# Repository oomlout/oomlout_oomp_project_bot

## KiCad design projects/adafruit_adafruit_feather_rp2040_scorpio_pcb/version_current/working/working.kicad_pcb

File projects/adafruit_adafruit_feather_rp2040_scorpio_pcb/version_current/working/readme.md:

# OOMP Project  
## Adafruit-Feather-RP2040-SCORPIO-PCB  by adafruit  
  
oomp key: oomp_projects_flat_adafruit_adafruit_feather_rp2040_scorpio_pcb  
(snippet of original readme)  
  
-- Adafruit Feather RP2040 SCORPIO 8 Channel NeoPixel Driver PCB  
  
<a href="http://www.adafruit.com/products/5650"><br/>  
Click here to purchase one from the Adafruit shop</a>  
  
PCB files for the Adafruit Feather RP2040 SCORPIO 8 Channel NeoPixel Driver.   
  
Format is EagleCAD schematic and board layout  
* https://www.adafruit.com/product/5650  
  
--- Description  
  
If there is one thing Adafruit is known for, its mega-blinky-fun-rainbow-LEDs. We just love sticking NeoPixels anywhere and everywhere. When we saw the new 'PIO' peripheral on the RP2040 from Raspberry Pi, we just knew it would be perfect for driving large quantities of NeoPixels. So we created this board, the Adafruit Feather RP2040 SCORPIO, designed specifically for NeoPixel (WS2812) driving but also good for various other PIO-based projects that want to take advantage of the Feather pinout with 8 separate consecutive outputs (or inputs).  
  
The RP2040 PIO state machine is perfect for LED driving: it can generate perfect waveforms, with up to 8 outputs concurrently, all through DMA. That means that you don't need to use any processor time to bit-bang-out the LED data. Just set up the buffer and tell the PIO peripheral to 'make it so' and it will shove that data to the 8 outputs without delay while your code can continue to read buttons, play music, run CircuitPython - whatever you like!  
  
The SCORPIO has a clever pinout, where all the standard Feather pins are the same as the   
  full source readme at [readme_src.md](readme_src.md)  
  
source repo at: [https://github.com/adafruit/Adafruit-Feather-RP2040-SCORPIO-PCB](https://github.com/adafruit/Adafruit-Feather-RP2040-SCORPIO-PCB)  
## Board  

## Schematic  

[schematic pdf](working_schematic.pdf)  
## Images

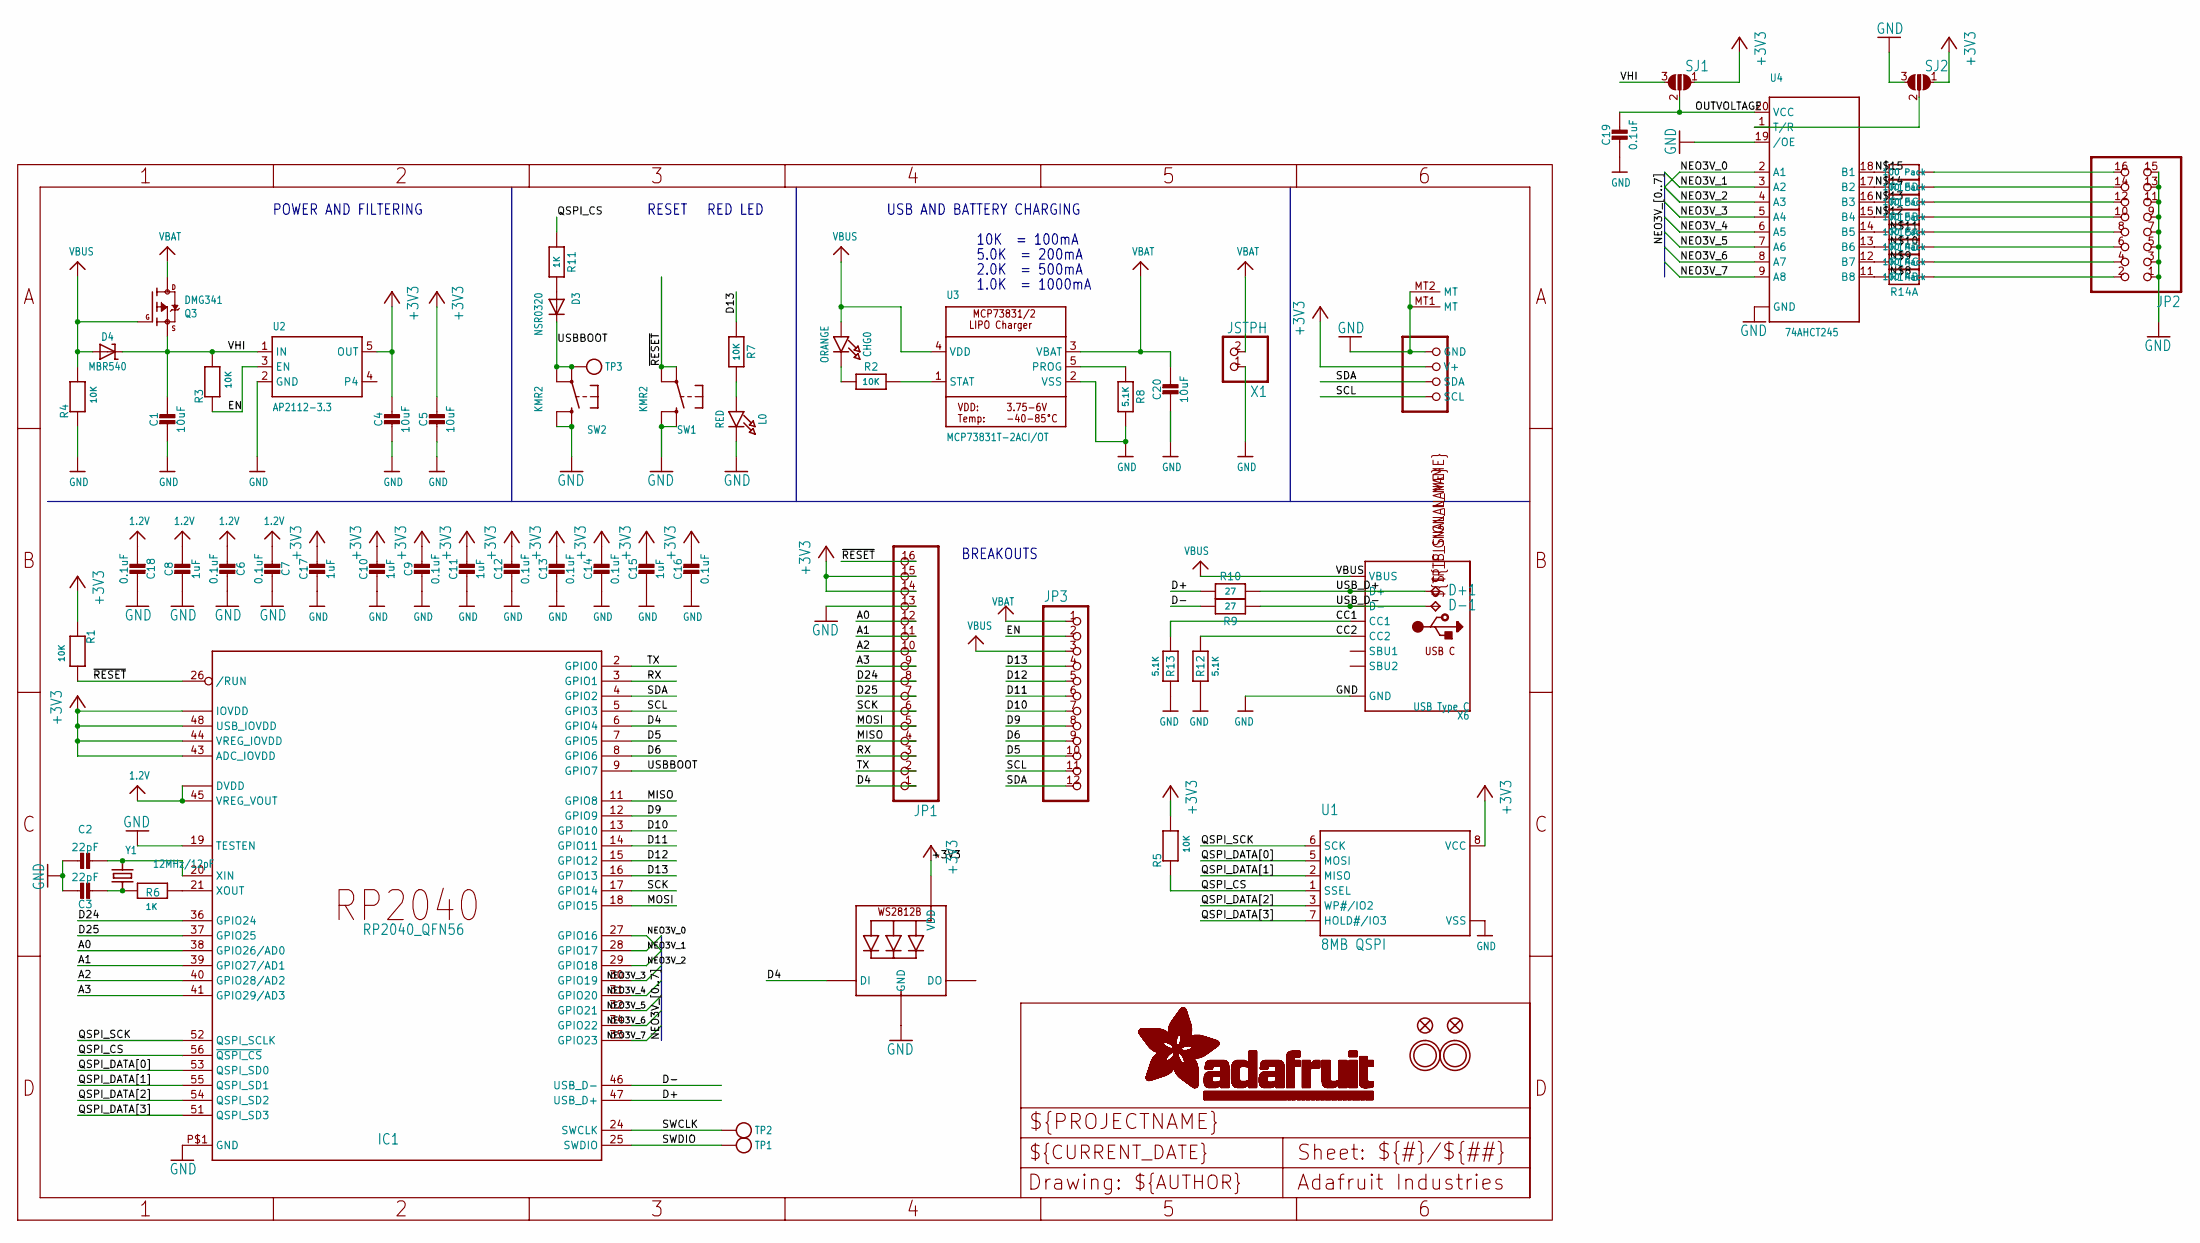
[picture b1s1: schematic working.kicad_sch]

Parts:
C1, C4, C5, C20: 10uF; 0805-NO
C2, C3: 22pF; _0402NO
C6, C7, C9, C12, C13, C14, C16, C18, C19: 0.1uF; _0402NO
C8, C10, C11, C15, C17: 1uF; 0603-NO
CHG0: ORANGE; CHIPLED_0603_NOOUTLINE
CONN1: STEMMA_I2C_QTRA; JST_SH4_RA
D3: NSR0320; SOD-323F
D4: MBR540; SOD-123
D+1: TPB1,27; B1,27
D-1: TPB1,27; B1,27
IC1: RP2040_QFN56; QFN56_7MM_REDUCEDEPAD
JP1: HEADER-1X16ROUND; 1X16_ROUND
JP2: HEADER-2X8; 2X08
JP3: HEADER-1X12; 1X12_ROUND
L0: RED; CHIPLED_0603_NOOUTLINE
LED1: WS2812B_SK6805_1515; SK6805_1515
Q3: DMG341; SOT23-R
R1, R2, R3, R4, R5, R7: 10K; 0603-NO
R6, R11: 1K; 0603-NO
R8, R12, R13: 5.1K; 0603-NO
R9, R10: 27; 0603-NO
R14, R15: 100 Pack; RESPACK_4X0402
SJ1, SJ2: SOLDERJUMPER_2WAY; SOLDERJUMPER_2WAY_OPEN_NOPASTE
SW1, SW2: KMR2; BTN_KMR2_4.6X2.8
TP1, TP2, TP3: TESTPOINTROUND1.5MMNO; TESTPOINT_ROUND_1.5MM_NO
U1: 8MB QSPI; USON8_4X4
U2: AP2112-3.3; SOT23-5; JLC_ROTATION 0
U3: MCP73831T-2ACI/OT; SOT23-5
U4: 74AHCT245; 20-DHVQFN
U$31, U$32: MOUNTINGHOLE2.5; MOUNTINGHOLE_2.5_PLATED
U$34, U$35: FIDUCIAL_1MM
X1: JSTPH; JSTPH2_BATT
X6: USB Type C; USB_C_CUSB31-CFM2AX-01-X
Y1: 12MHz/12pF; CRYSTAL_2.5X2

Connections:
1.2V: C6.2, C7.2, C8.1, C18.2, IC1.23 (DVDD), IC1.45 (VREG_VOUT), IC1.50 (DVDD)
+3V3: C4.1, C5.1, C9.1, C10.1, C11.1, C12.1, C13.1, C14.1, C15.1, C16.1, C17.1, CONN1.2 (V+), IC1.1 (IOVDD), IC1.10 (IOVDD), IC1.22 (IOVDD), IC1.33 (IOVDD), IC1.42 (IOVDD), IC1.43 (ADC_IOVDD), IC1.44 (VREG_IOVDD), IC1.48 (USB_IOVDD), IC1.49 (IOVDD), JP1.14, JP1.15, LED1.2 (VDD), R1.1, R5.2, SJ1.1, SJ2.1, U1.8 (VCC), U2.5 (OUT)
A0: IC1.38 (GPIO26/AD0), JP1.12
A1: IC1.39 (GPIO27/AD1), JP1.11
A2: IC1.40 (GPIO28/AD2), JP1.10
A3: IC1.41 (GPIO29/AD3), JP1.9
CC1: R13.2, X6.A5 (CC1)
CC2: R12.2, X6.B5 (CC2)
D4: IC1.6 (GPIO4), JP1.1, LED1.1 (DI)
D5: IC1.7 (GPIO5), JP3.10
D6: IC1.8 (GPIO6), JP3.9
D9: IC1.12 (GPIO9), JP3.8
D10: IC1.13 (GPIO10), JP3.7
D11: IC1.14 (GPIO11), JP3.6
D12: IC1.15 (GPIO12), JP3.5
D13: IC1.16 (GPIO13), JP3.4, R7.1
D24: IC1.36 (GPIO24), JP1.8
D25: IC1.37 (GPIO25), JP1.7
D+: IC1.47 (USB_D+), R10.2
D-: IC1.46 (USB_D-), R9.2
EN: JP3.2, R3.1, U2.3 (EN)
GND: C1.2, C2.1, C3.1, C4.2, C5.2, C6.1, C7.1, C8.2, C9.2, C10.2, C11.2, C12.2, C13.2, C14.2, C15.2, C16.2, C17.2, C18.1, C19.2, C20.2, CONN1.1 (GND), CONN1.MT1 (MT), CONN1.MT2 (MT), IC1.19 (TESTEN), IC1.P$1 (GND), JP1.13, JP2.1, JP2.3, JP2.5, JP2.7, JP2.9, JP2.11, JP2.13, JP2.15, L0.C, LED1.4 (GND), R4.1, R8.2, R12.1, R13.1, SJ2.3, SW1.B (S), SW1.B' (S1), SW2.B (S), SW2.B' (S1), U1.4 (VSS), U1.PAD (VSS), U2.2 (GND), U3.2 (VSS), U4.10 (GND), U4.19 (/OE), U4.21 (GND), X1.1, X6.A1B12 (GND), X6.B1A12 (GND)
MISO: IC1.11 (GPIO8), JP1.4
MOSI: IC1.18 (GPIO15), JP1.5
unnamed: CHG0.C, R2.1
unnamed: L0.A, R7.2
unnamed: R2.2, U3.1 (STAT)
unnamed: R8.1, U3.5 (PROG)
unnamed: C2.2, IC1.20 (XIN), Y1.3 (2)
unnamed: C3.2, R6.1, Y1.1
unnamed: IC1.21 (XOUT), R6.2
unnamed: R14.8 (2), U4.11 (B8)
unnamed: R14.7 (2), U4.12 (B7)
unnamed: R14.6 (2), U4.13 (B6)
unnamed: R14.5 (2), U4.14 (B5)
unnamed: R15.8 (2), U4.15 (B4)
unnamed: R15.7 (2), U4.16 (B3)
unnamed: R15.6 (2), U4.17 (B2)
unnamed: R15.5 (2), U4.18 (B1)
unnamed: D3.A, R11.2
unnamed: SJ2.2, U4.1 (T/R)
NEO0: JP2.16, R15.4 (1)
NEO1: JP2.14, R15.3 (1)
NEO2: JP2.12, R15.2 (1)
NEO3: JP2.10, R15.1
NEO3V_0: IC1.27 (GPIO16), U4.2 (A1)
NEO3V_1: IC1.28 (GPIO17), U4.3 (A2)
NEO3V_2: IC1.29 (GPIO18), U4.4 (A3)
NEO3V_3: IC1.30 (GPIO19), U4.5 (A4)
NEO3V_4: IC1.31 (GPIO20), U4.6 (A5)
NEO3V_5: IC1.32 (GPIO21), U4.7 (A6)
NEO3V_6: IC1.34 (GPIO22), U4.8 (A7)
NEO3V_7: IC1.35 (GPIO23), U4.9 (A8)
NEO4: JP2.8, R14.4 (1)
NEO5: JP2.6, R14.3 (1)
NEO6: JP2.4, R14.2 (1)
NEO7: JP2.2, R14.1
OUTVOLTAGE: C19.1, SJ1.2, U4.20 (VCC)
QSPI_CS: IC1.56 (~QSPI_CS), R5.1, R11.1, U1.1 (SSEL)
QSPI_DATA[0]: IC1.53 (QSPI_SD0), U1.5 (MOSI)
QSPI_DATA[1]: IC1.55 (QSPI_SD1), U1.2 (MISO)
QSPI_DATA[2]: IC1.54 (QSPI_SD2), U1.3 (WP#/IO2)
QSPI_DATA[3]: IC1.51 (QSPI_SD3), U1.7 (HOLD#/IO3)
QSPI_SCK: IC1.52 (QSPI_SCLK), U1.6 (SCK)
RX: IC1.3 (GPIO1), JP1.3
SCK: IC1.17 (GPIO14), JP1.6
SCL: CONN1.4 (SCL), IC1.5 (GPIO3), JP3.11
SDA: CONN1.3 (SDA), IC1.4 (GPIO2), JP3.12
SWCLK: IC1.24 (SWCLK), TP2.P$1
SWDIO: IC1.25 (SWDIO), TP1.P$1
TX: IC1.2 (GPIO0), JP1.2
USBBOOT: D3.C, IC1.9 (GPIO7), SW2.A, SW2.A' (P1), TP3.P$1
USB_D+: D+1.TP, R10.1, X6.A6 (D+), X6.B6 (D+)
USB_D-: D-1.TP, R9.1, X6.A7 (D-), X6.B7 (D-)
VBAT: C20.1, JP3.1, Q3.3 (D), U3.3 (VBAT), X1.2
VBUS: CHG0.A, D4.A, JP3.3, Q3.1 (G), R4.2, U3.4 (VDD), X6.A4B9 (VBUS), X6.B4A9 (VBUS)
VHI: C1.1, D4.C, Q3.2 (S), R3.2, SJ1.3, U2.1 (IN)
~RESET: IC1.26 (/RUN), JP1.16, R1.2, SW1.A, SW1.A' (P1)

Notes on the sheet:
5.0K = 200mA
POWER AND FILTERING
10K = 100mA
BREAKOUTS
1.0K = 1000mA
USB AND BATTERY CHARGING
RESET
RED LED
2.0K = 500mA

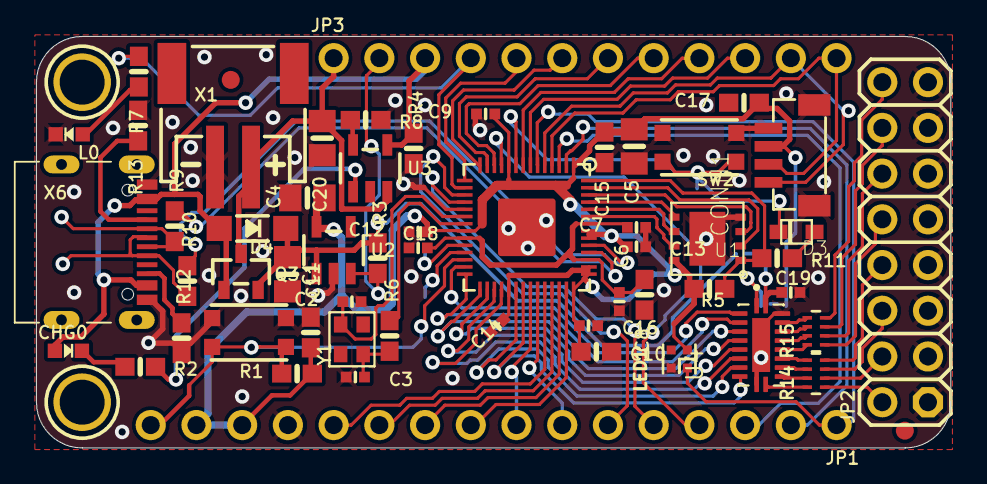
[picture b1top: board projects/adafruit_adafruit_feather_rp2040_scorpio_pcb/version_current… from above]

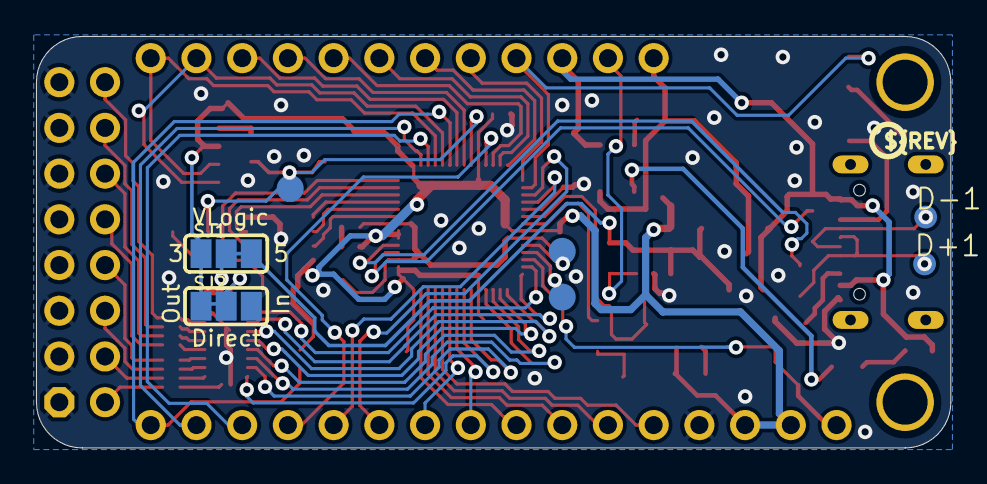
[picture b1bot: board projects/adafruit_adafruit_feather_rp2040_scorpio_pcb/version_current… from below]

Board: 2 copper layers, 50.8 x 22.9 mm, 69 parts (9 on the bottom side), 78 nets.

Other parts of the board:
U$12: SCORPIO_TOP
U$13: PCBFEAT-REV-040
U$28: SCORPIO_BOT

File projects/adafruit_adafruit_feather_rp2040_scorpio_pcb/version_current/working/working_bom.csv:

Row,Description,Part,References,Value,Footprint,Quantity Per PCB,Status,Datasheet,JLC_ROTATION,REV
1,,CAP_CERAMIC_0402NO,C2 C3,22pF,_0402NO,2, ,,,
2,,CAP_CERAMIC_0402NO,C6 C7 C9 C12 C13 C14 C16 C18 C19,0.1uF,_0402NO,9, ,,,
3,,CAP_CERAMIC0603_NO,C8 C10 C11 C15 C17,1uF,0603-NO,5, ,,,
4,,CAP_CERAMIC0805-NOOUTLINE,C1 C4 C5 C20,10uF,0805-NO,4, ,,,A
5,,LED0603_NOOUTLINE,CHG0,ORANGE,CHIPLED_0603_NOOUTLINE,1, ,,,
6,,STEMMA_I2C_QTRA,CONN1,STEMMA_I2C_QTRA,JST_SH4_RA,1, ,,,
7,,DIODE-SCHOTTKYSOD-123,D4,MBR540,SOD-123,1, ,,,
8,,DIODESOD-323F,D3,NSR0320,SOD-323F,1, ,,,
9,,"TPB1,27",D+1 D-1,"TPB1,27","B1,27",2, ,,,
10,,RP2040_QFN56,IC1,RP2040_QFN56,QFN56_7MM_REDUCEDEPAD,1, ,,,
11,,HEADER-1X12,JP3,HEADER-1X12,1X12_ROUND,1, ,,,
12,,HEADER-1X16ROUND,JP1,HEADER-1X16ROUND,1X16_ROUND,1, ,,,
13,,HEADER-2X8,JP2,HEADER-2X8,2X08,1, ,,,
14,,LED0603_NOOUTLINE,L0,RED,CHIPLED_0603_NOOUTLINE,1, ,,,
15,,WS2812B_SK6805_1515,LED1,WS2812B_SK6805_1515,SK6805_1515,1, ,,,
16,,MOSFET-P,Q3,DMG341,SOT23-R,1, ,,,
17,,RESISTOR_0603_NOOUT,R9 R10,27,0603-NO,2, ,,,
18,,RESISTOR_4PACK_0804,R14 R15,100 Pack,RESPACK_4X0402,2, ,,,
19,,RESISTOR_0603_NOOUT,R6 R11,1K,0603-NO,2, ,,,
20,,RESISTOR_0603_NOOUT,R8 R12 R13,5.1K,0603-NO,3, ,,,
21,,RESISTOR_0603_NOOUT,R1 R2 R3 R4 R5 R7,10K,0603-NO,6, ,,,
22,,SWITCH_TACT_SMT4.6X2.8,SW1 SW2,KMR2,BTN_KMR2_4.6X2.8,2, ,,,
23,,74LCX245_QFN20,U4,74AHCT245,20-DHVQFN,1, ,,,
24,,SPIFLASH_8PIN_4X4,U1,8MB QSPI,USON8_4X4,1, ,,,
25,,VREG_SOT23-5,U2,AP2112-3.3,SOT23-5,1, ,,0,
26,,MCP73831/2,U3,MCP73831T-2ACI/OT,SOT23-5,1, ,,,
27,,CON_JST_PH_2PIN_BATT,X1,JSTPH,JSTPH2_BATT,1, ,,,
28,,USB_C,X6,USB Type C,USB_C_CUSB31-CFM2AX-01-X,1, ,,,
29,,CRYSTAL2.5X2.0,Y1,12MHz/12pF,CRYSTAL_2.5X2,1, ,,,





Project info:
Schematic:,working
Variant:,default
Revision:,
Date:,2023-08-02_17-08-33
KiCad Version:,7.0.6-7.0.6~ubuntu22.04.1
Statistics:
Component Groups:,29
Component Count:,57 (0 SMD/ 0 THT)
Fitted Components:,57 (0 SMD/ 0 THT)
Number of PCBs:,1
Total Components:,57

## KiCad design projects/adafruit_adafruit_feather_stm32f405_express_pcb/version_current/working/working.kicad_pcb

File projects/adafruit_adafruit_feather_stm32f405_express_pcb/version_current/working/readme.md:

# OOMP Project  
## Adafruit-Feather-STM32F405-Express-PCB  by adafruit  
  
oomp key: oomp_projects_flat_adafruit_adafruit_feather_stm32f405_express_pcb  
(snippet of original readme)  
  
-- Adafruit Adafruit Feather STM32F405 Express PCB  
  
<a href="http://www.adafruit.com/products/4382"><br/>  
Click here to purchase one from the Adafruit shop</a>  
  
PCB files for the Adafruit Adafruit Feather STM32F405 Express.   
  
Format is EagleCAD schematic and board layout  
* https://www.adafruit.com/product/4382  
  
--- Description  
  
ST takes flight in this upcoming Feather board. The new STM32F405 Feather (video) that we designed runs CircuitPython at a blistering 168MHz – our fastest CircuitPython board ever! We put a STEMMA QT / Qwiic port on the end, so you can really easily plug and play I2C sensors.  
  
This Feather has lots of goodies:  
  
* STM32F405 Cortex M4 with FPU and 1MB Flash, 168MHz speed  
* 192KB RAM total - 128 KB RAM for general usage + 64 KB program-only/cache RAM  
* 3.3V logic, but almost all pins are 5V compliant!  
* USB C power and data - our first USB C Feather!  
* LiPo connector and charger  
* SD socket on the bottom, connected to SDIO port  
* 2 MB SPI Flash chip  
* Built in NeoPixel indicator  
* I2C, UART, GPIO, ADCs, DACs  
* Qwiic/STEMMA-QT connector for fast I2C connectivity  
* We use the built-in USB DFU bootloader to load firmware. It does not come with a UF2 bootloader.  
  
With CircuitPython basics running on this board, it's fast to get all our drivers working, then use the built in plotter in Mu to instantly get sensor data displaying within 3 minutes of unboxing.  
  
You can use MicroPython, CircuitPython or Arduino IDE  
  full source readme at [readme_src.md](readme_src.md)  
  
source repo at: [https://github.com/adafruit/Adafruit-Feather-STM32F405-Express-PCB](https://github.com/adafruit/Adafruit-Feather-STM32F405-Express-PCB)  
## Board  

## Schematic  

[schematic pdf](working_schematic.pdf)  
## Images

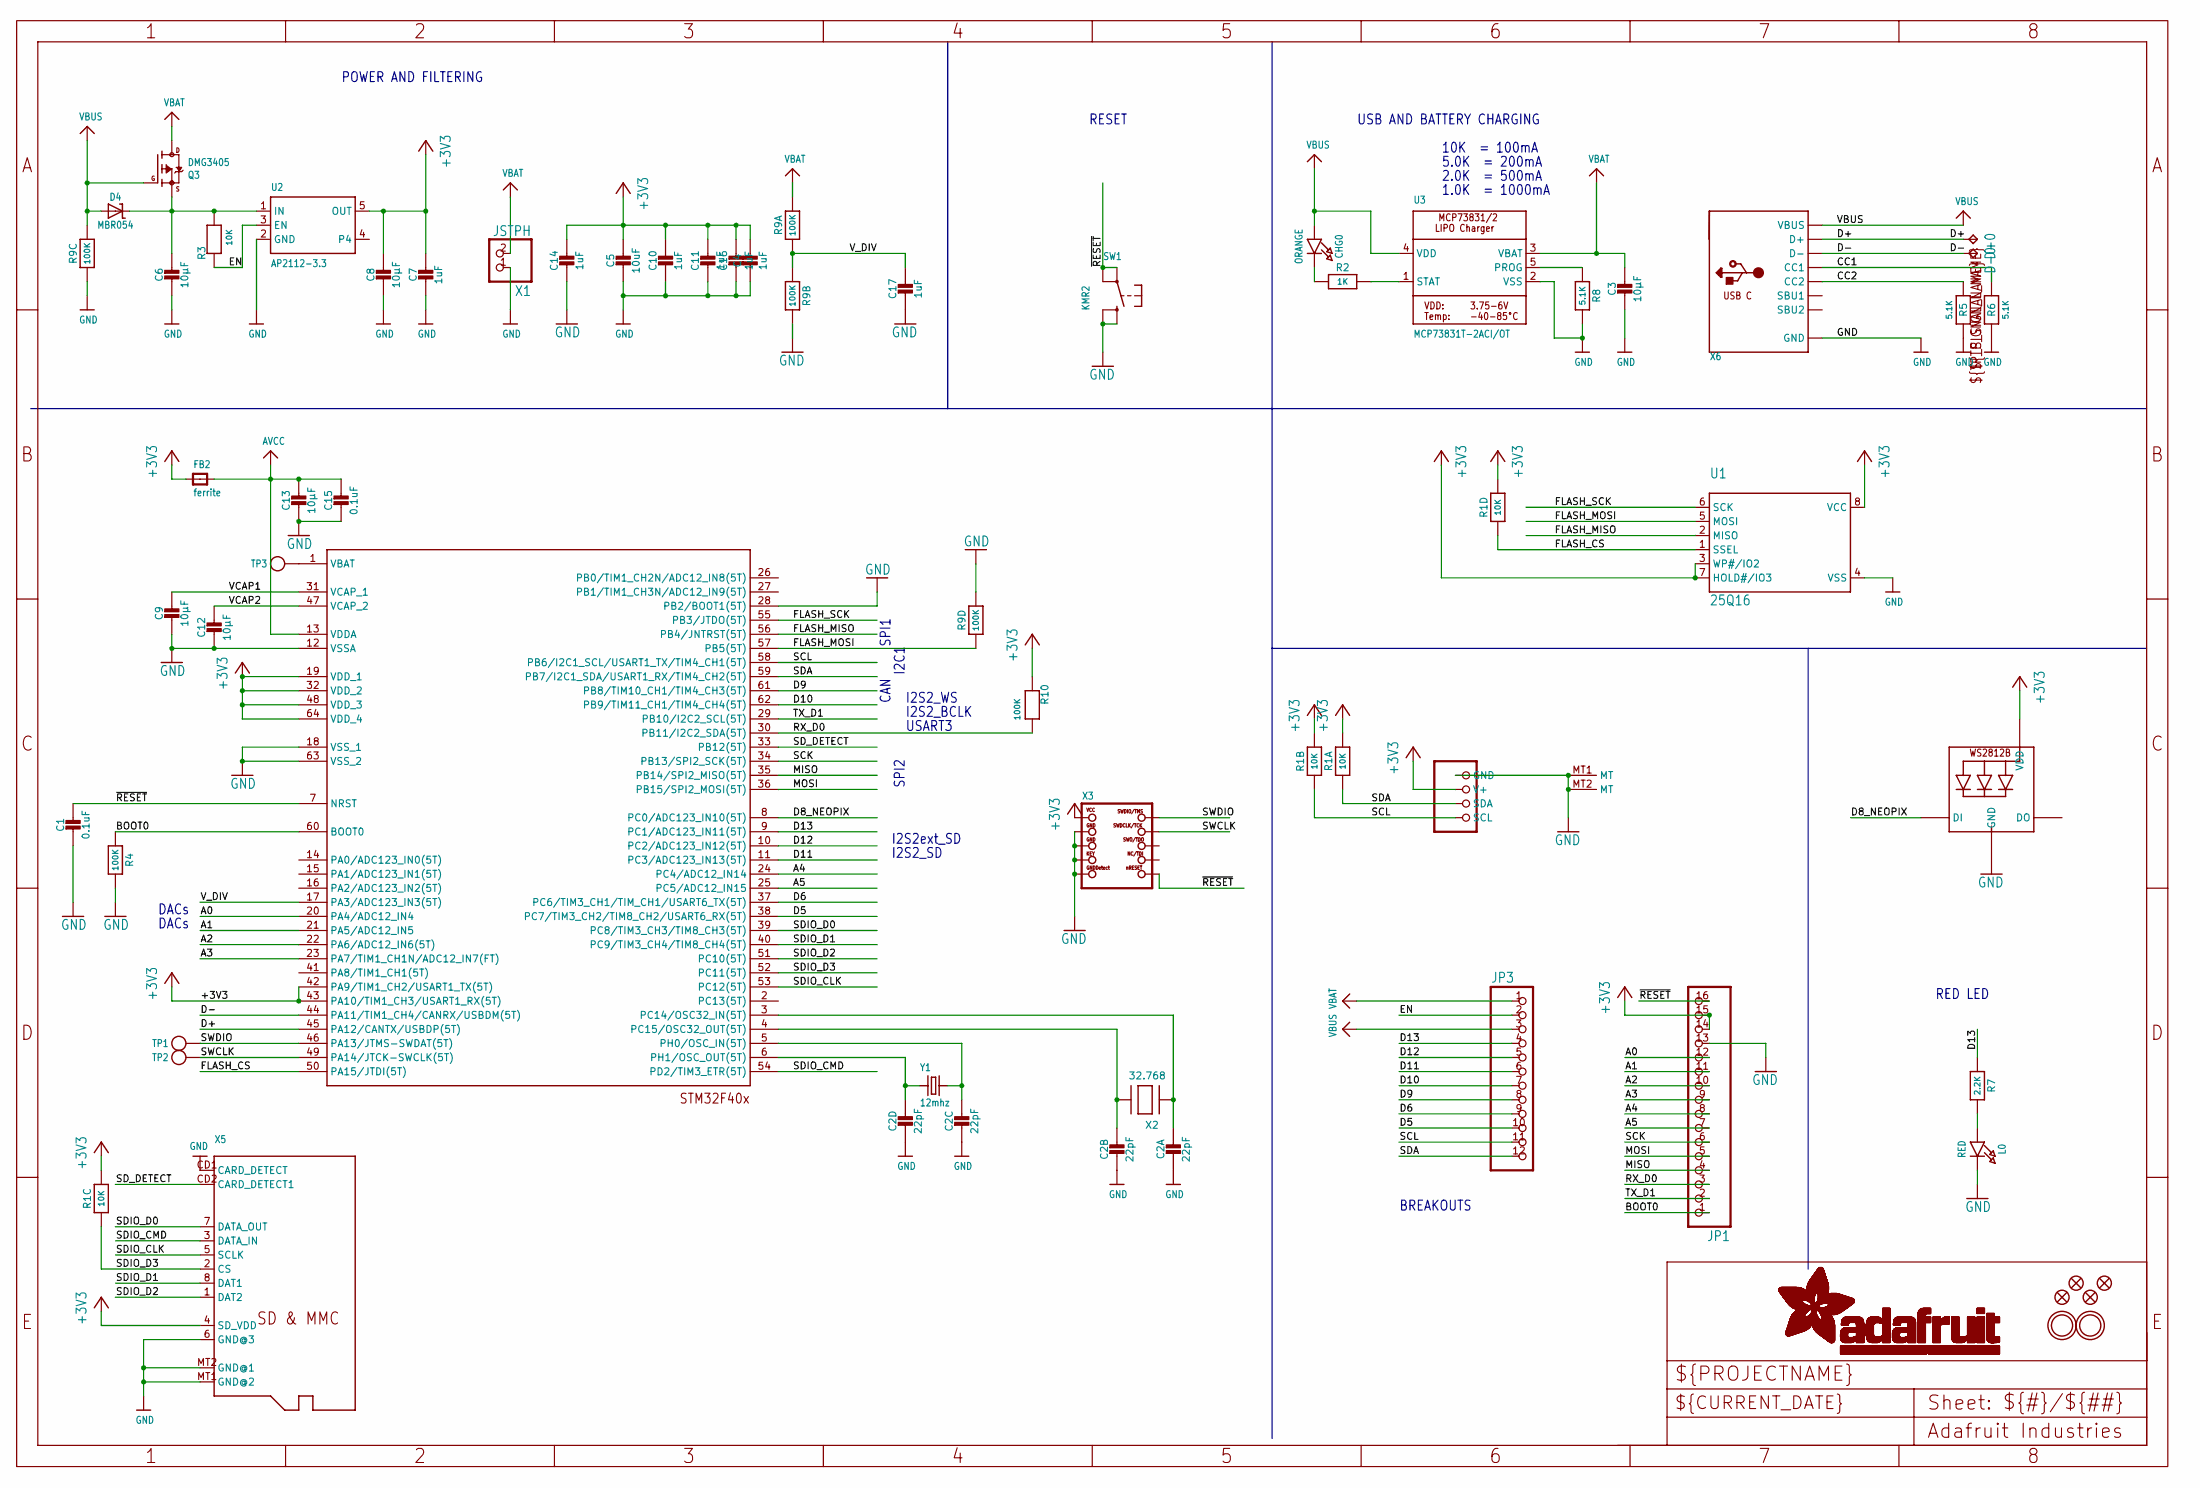
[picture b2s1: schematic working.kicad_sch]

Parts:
C1, C15: 0.1uF; 0603-NO
C2: 22pF; RESPACK_4X0603
C3, C6, C8, C9, C12, C13: 10µF; 0805-NO
C4, C7, C10, C11, C14, C16, C17: 1uF; 0603-NO
C5: 10uF; 0805-NO
CHG0: ORANGE; CHIPLED_0805_NOOUTLINE
CONN1: STEMMA_I2C_QT; JST_SH4
D4: MBR054; SOD-123
D+0: TPB1,27; B1,27
D-0: TPB1,27; B1,27
FB2: ferrite; 0805-NO
JP1: HEADER-1X16ROUND; 1X16_ROUND
JP3: HEADER-1X12; 1X12_ROUND
L0: RED; CHIPLED_0805_NOOUTLINE
LED1: WS2812B3535; LED3535
Q3: DMG3405; SOT23-R
R1: 10K; RESPACK_4X0603_NO
R2: 1K; 0603-NO
R3: 10K; 0603-NO
R4, R10: 100K; 0603-NO
R5, R6, R8: 5.1K; 0603-NO
R7: 2.2K; 0603-NO
R9: 100K; RESPACK_4X0603_NO
SW1: KMR2; BTN_KMR2_4.6X2.8
TP1, TP2, TP3: TESTPOINTROUND1.5MM; TESTPOINT_ROUND_1.5MM
U1: 25Q16; SOIC8_150MIL
U2: AP2112-3.3; SOT23-5
U3: MCP73831T-2ACI/OT; SOT23-5
U$3: STM32F405R; TQFP64
U$5, U$34, U$35, U$37: FIDUCIAL_1MM
U$31, U$32: MOUNTINGHOLE2.5; MOUNTINGHOLE_2.5_PLATED
X1: JSTPH; JSTPH2
X2: 32.768; XTAL3215
X3: JTAG-CORTEX; 2X05_1.27MM_SMT
X5: MICROSD
X6: USB_C; USB_C_CUSB31-CFM2AX-01-X
Y1: 12mhz; CRYSTAL_2.5X2

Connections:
+3V3: C4.1, C5.1, C7.1, C8.1, C10.1, C11.1, C14.1, C16.1, CONN1.2 (V+), FB2.1, JP1.14, JP1.15, LED1.2 (VDD), R1.5 (2), R1.6 (2), R1.7 (2), R1.8 (2), R10.1, U1.3 (WP#/IO2), U1.7 (HOLD#/IO3), U1.8 (VCC), U2.5 (OUT), U$3.19 (VDD_1), U$3.32 (VDD_2), U$3.42 (PA9/TIM1_CH2/USART1_TX(5T)), U$3.43 (PA10/TIM1_CH3/USART1_RX(5T)), U$3.48 (VDD_3), U$3.64 (VDD_4), X3.1 (VCC), X5.4 (SD_VDD)
A0: JP1.12, U$3.20 (PA4/ADC12_IN4)
A1: JP1.11, U$3.21 (PA5/ADC12_IN5)
A2: JP1.10, U$3.22 (PA6/ADC12_IN6(5T))
A3: JP1.9, U$3.23 (PA7/TIM1_CH1N/ADC12_IN7(FT))
A4: JP1.8, U$3.24 (PC4/ADC12_IN14)
A5: JP1.7, U$3.25 (PC5/ADC12_IN15)
AVCC: C13.1, C15.1, FB2.2, U$3.13 (VDDA)
BATTERY: TP3.P$1, U$3.1 (VBAT)
BOOT0: JP1.1, R4.1, U$3.60 (BOOT0)
CC1: R6.2, X6.A5 (CC1)
CC2: R5.2, X6.B5 (CC2)
D5: JP3.10, U$3.38 (PC7/TIM3_CH2/TIM8_CH2/USART6_RX(5T))
D6: JP3.9, U$3.37 (PC6/TIM3_CH1/TIM_CH1/USART6_TX(5T))
D8_NEOPIX: LED1.1 (DI), U$3.8 (PC0/ADC123_IN10(5T))
D9: JP3.8, U$3.61 (PB8/TIM10_CH1/TIM4_CH3(5T))
D10: JP3.7, U$3.62 (PB9/TIM11_CH1/TIM4_CH4(5T))
D11: JP3.6, U$3.11 (PC3/ADC123_IN13(5T))
D12: JP3.5, U$3.10 (PC2/ADC123_IN12(5T))
D13: JP3.4, R7.1, U$3.9 (PC1/ADC123_IN11(5T))
D+: D+0.TP, U$3.45 (PA12/CANTX/USBDP(5T)), X6.A6 (D+), X6.B6 (D+)
D-: D-0.TP, U$3.44 (PA11/TIM1_CH4/CANRX/USBDM(5T)), X6.A7 (D-), X6.B7 (D-)
EN: JP3.2, R3.1, U2.3 (EN)
FLASH_CS: R1.4 (1), U1.1 (SSEL), U$3.50 (PA15/JTDI(5T))
FLASH_MISO: U1.2 (MISO), U$3.56 (PB4/JNTRST(5T))
FLASH_MOSI: R9.4 (1), U1.5 (MOSI), U$3.57 (PB5(5T))
FLASH_SCK: U1.6 (SCK), U$3.55 (PB3/JTDO(5T))
GND: C1.2, C2.5 (2), C2.6 (2), C2.7 (2), C2.8 (2), C3.2, C4.2, C5.2, C6.2, C7.2, C8.2, C9.2, C10.2, C11.2, C12.2, C13.2, C14.2, C15.2, C16.2, C17.2, CONN1.1 (GND), CONN1.MT1 (MT), CONN1.MT2 (MT), JP1.13, L0.C, LED1.4 (GND), R4.2, R5.1, R6.1, R8.2, R9.3 (1), R9.5 (2), R9.7 (2), SW1.B (S), SW1.B' (S1), U1.4 (VSS), U2.2 (GND), U3.2 (VSS), U$3.12 (VSSA), U$3.18 (VSS_1), U$3.28 (PB2/BOOT1(5T)), U$3.63 (VSS_2), X1.1, X3.3 (GND@1), X3.5 (GND@2), X3.7 (KEY), X3.9 (GNDDETECT), X5.6 (GND@3), X5.CD1 (CARD_DETECT), X5.MT1 (GND@2), X5.MT2 (GND@1), X6.A1B12 (GND), X6.B1A12 (GND)
MISO: JP1.4, U$3.35 (PB14/SPI2_MISO(5T))
MOSI: JP1.5, U$3.36 (PB15/SPI2_MOSI(5T))
unnamed: CHG0.C, R2.1
unnamed: L0.A, R7.2
unnamed: R2.2, U3.1 (STAT)
unnamed: R8.1, U3.5 (PROG)
unnamed: C2.4 (1), U$3.3 (PC14/OSC32_IN(5T)), X2.P$1
unnamed: C2.2 (1), U$3.5 (PH0/OSC_IN(5T)), Y1.3 (2)
unnamed: C2.3 (1), U$3.4 (PC15/OSC32_OUT(5T)), X2.P$2
unnamed: C2.1, U$3.6 (PH1/OSC_OUT(5T)), Y1.1
RX_D0: JP1.3, R10.2, U$3.30 (PB11/I2C2_SDA(5T))
SCK: JP1.6, U$3.34 (PB13/SPI2_SCK(5T))
SCL: CONN1.4 (SCL), JP3.11, R1.2 (1), U$3.58 (PB6/I2C1_SCL/USART1_TX/TIM4_CH1(5T))
SDA: CONN1.3 (SDA), JP3.12, R1.1, U$3.59 (PB7/I2C1_SDA/USART1_RX/TIM4_CH2(5T))
SDIO_CLK: U$3.53 (PC12(5T)), X5.5 (SCLK)
SDIO_CMD: U$3.54 (PD2/TIM3_ETR(5T)), X5.3 (DATA_IN)
SDIO_D0: U$3.39 (PC8/TIM3_CH3/TIM8_CH3(5T)), X5.7 (DATA_OUT)
SDIO_D1: U$3.40 (PC9/TIM3_CH4/TIM8_CH4(5T)), X5.8 (DAT1)
SDIO_D2: U$3.51 (PC10(5T)), X5.1 (DAT2)
SDIO_D3: R1.3 (1), U$3.52 (PC11(5T)), X5.2 (CS)
SD_DETECT: U$3.33 (PB12(5T)), X5.CD2 (CARD_DETECT1)
SWCLK: TP2.P$1, U$3.49 (PA14/JTCK-SWCLK(5T)), X3.4 (SWDCLK)
SWDIO: TP1.P$1, U$3.46 (PA13/JTMS-SWDAT(5T)), X3.2 (SWDIO)
TX_D1: JP1.2, U$3.29 (PB10/I2C2_SCL(5T))
VBAT: C3.1, JP3.1, Q3.3 (D), R9.8 (2), U3.3 (VBAT), X1.2
VBUS: CHG0.A, D4.A, JP3.3, Q3.1 (G), R9.6 (2), U3.4 (VDD), X6.A4B9 (VBUS), X6.B4A9 (VBUS)
VCAP1: C9.1, U$3.31 (VCAP_1)
VCAP2: C12.1, U$3.47 (VCAP_2)
VHI: C6.1, D4.C, Q3.2 (S), R3.2, U2.1 (IN)
V_DIV: C17.1, R9.1, R9.2 (1), U$3.17 (PA3/ADC123_IN3(5T))
~RESET: C1.1, JP1.16, SW1.A, SW1.A' (P1), U$3.7 (NRST), X3.10 (NRESET)

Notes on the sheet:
BREAKOUTS
POWER AND FILTERING
DACs
USART3
1.0K = 1000mA
I2S2_BCLK
CAN
RESET
10K = 100mA
I2C1
SPI2
USB AND BATTERY CHARGING
I2S2ext_SD
I2S2_SD
RED LED
SPI1
2.0K = 500mA
5.0K = 200mA
I2S2_WS

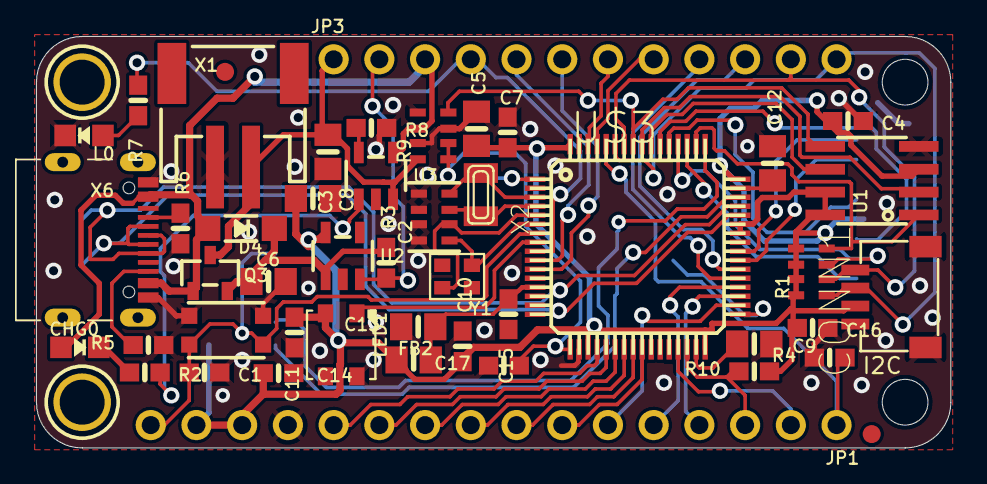
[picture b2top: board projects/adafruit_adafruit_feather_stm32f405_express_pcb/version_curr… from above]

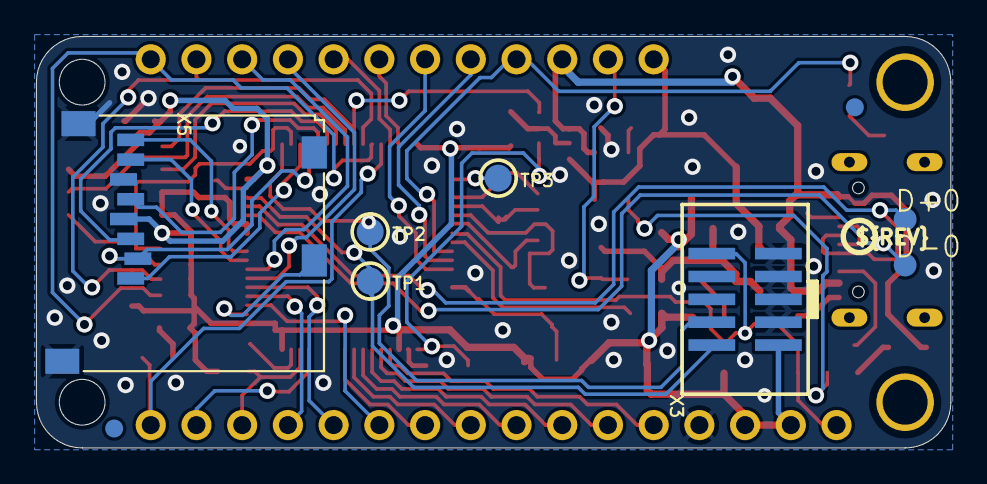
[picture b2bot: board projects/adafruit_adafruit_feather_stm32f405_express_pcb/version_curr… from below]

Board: 2 copper layers, 50.8 x 22.9 mm, 63 parts (11 on the bottom side), 59 nets.

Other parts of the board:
@HOLE0, @HOLE1: (no value)
U$13: PCBFEAT-REV-040
U$24: FEATHER_STM32F405_TOP
U$40: FEATHER_STM32F405_BOT

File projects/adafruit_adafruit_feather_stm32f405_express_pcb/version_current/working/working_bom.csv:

Row,Description,Part,References,Value,Footprint,Quantity Per PCB,Status,Datasheet,REV
1,,CAP_4PACK1206,C2,22pF,RESPACK_4X0603,1, ,,
2,,CAP_CERAMIC0603_NO,C1 C15,0.1uF,0603-NO,2, ,,
3,,CAP_CERAMIC0603_NO,C4 C7 C10 C11 C14 C16 C17,1uF,0603-NO,7, ,,
4,,CAP_CERAMIC0805-NOOUTLINE,C3 C5 C6 C8 C9 C12 C13,10µF,0805-NO,7, ,,B
5,,LED0805_NOOUTLINE,CHG0,ORANGE,CHIPLED_0805_NOOUTLINE,1, ,,
6,,STEMMA_I2C_QT,CONN1,STEMMA_I2C_QT,JST_SH4,1, ,,
7,,DIODE-SCHOTTKYSOD-123,D4,MBR054,SOD-123,1, ,,
8,,"TPB1,27",D+0 D-0,"TPB1,27","B1,27",2, ,,
9,,FERRITE-0805NO,FB2,ferrite,0805-NO,1, ,,
10,,HEADER-1X12,JP3,HEADER-1X12,1X12_ROUND,1, ,,
11,,HEADER-1X16ROUND,JP1,HEADER-1X16ROUND,1X16_ROUND,1, ,,
12,,LED0805_NOOUTLINE,L0,RED,CHIPLED_0805_NOOUTLINE,1, ,,
13,,WS2812B3535,LED1,WS2812B3535,LED3535,1, ,,
14,,MOSFET-P,Q3,DMG3405,SOT23-R,1, ,,
15,,RESISTOR_0603_NOOUT,R2,1K,0603-NO,1, ,,
16,,RESISTOR_0603_NOOUT,R7,2.2K,0603-NO,1, ,,
17,,RESISTOR_0603_NOOUT,R5 R6 R8,5.1K,0603-NO,3, ,,
18,,RESISTOR_4PACK_NO,R1,10K,RESPACK_4X0603_NO,1, ,,
19,,RESISTOR_0603_NOOUT,R3,10K,0603-NO,1, ,,
20,,RESISTOR_0603_NOOUT,R4 R10,100K,0603-NO,2, ,,
21,,RESISTOR_4PACK_NO,R9,100K,RESPACK_4X0603_NO,1, ,,
22,,SWITCH_TACT_SMT4.6X2.8,SW1,KMR2,BTN_KMR2_4.6X2.8,1, ,,
23,,SPIFLASH_8PIN,U1,25Q16,SOIC8_150MIL,1, ,,
24,,VREG_SOT23-5,U2,AP2112-3.3,SOT23-5,1, ,,
25,,MCP73831/2,U3,MCP73831T-2ACI/OT,SOT23-5,1, ,,
26,,STM32F405R,U$3,STM32F405R,TQFP64,1, ,,
27,,XTAL-3.2X1.5,X2,32.768,XTAL3215,1, ,,
28,,CON_JST_PH_2PIN,X1,JSTPH,JSTPH2,1, ,,
29,,JTAG-CORTEX,X3,JTAG-CORTEX,2X05_1.27MM_SMT,1, ,,
30,,MICROSD,X5,MICROSD,MICROSD,1, ,,
31,,USB_C,X6,USB_C,USB_C_CUSB31-CFM2AX-01-X,1, ,,
32,,CRYSTAL2.5X2.0,Y1,12mhz,CRYSTAL_2.5X2,1, ,,





Project info:
Schematic:,working
Variant:,default
Revision:,
Date:,2023-08-02_17-08-33
KiCad Version:,7.0.6-7.0.6~ubuntu22.04.1
Statistics:
Component Groups:,32
Component Count:,49 (0 SMD/ 0 THT)
Fitted Components:,49 (0 SMD/ 0 THT)
Number of PCBs:,1
Total Components:,49

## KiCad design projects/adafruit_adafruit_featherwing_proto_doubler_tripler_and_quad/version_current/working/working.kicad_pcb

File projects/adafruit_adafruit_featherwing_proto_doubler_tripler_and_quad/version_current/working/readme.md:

# OOMP Project  
## Adafruit-FeatherWing-Proto-Doubler-Tripler-and-Quad  by adafruit  
  
oomp key: oomp_projects_flat_adafruit_adafruit_featherwing_proto_doubler_tripler_and_quad  
(snippet of original readme)  
  
-- FeatherWing Proto, Doubler, Tripler and Quad PCBs  
  
<br/>  
<br/>  
<br/>  
<br/>  
&nbsp;   
  
Click the picture or one of the links below to purchase from the Adafruit shop  
  
PCB files for the Adafruit Feather Wing Proto, Doubler, Tripler and Quad  
  
Format is EagleCAD schematic and board layout   
  
Click to order the boards of your choice  
 * FeatherWing Proto https://www.adafruit.com/products/2884  
 * FeatherWing Doubler https://www.adafruit.com/products/2890  
 * FeatherWing Tripler https://www.adafruit.com/products/3417  
 * FeatherWing Quad 2x2 https://www.adafruit.com/product/4253  
 * FeatherWing Quad Side by Side https://www.adafruit.com/product/4254  
  
--- Description  
  
These are the FeatherWing Proto, Doubler, Tripler and Quad - prototyping add-ons for all Feather boards. Using our [Feather Stacking Headers](https://www.adafruit.com/products/2830) or [Feather Female Headers](http://www.adafruit.com/products/2886) you can connect a FeatherWing on top or bottom of your Feather board and let  
  full source readme at [readme_src.md](readme_src.md)  
  
source repo at: [https://github.com/adafruit/Adafruit-FeatherWing-Proto-Doubler-Tripler-and-Quad](https://github.com/adafruit/Adafruit-FeatherWing-Proto-Doubler-Tripler-and-Quad)  
## Board  

## Schematic  

[schematic pdf](working_schematic.pdf)  
## Images

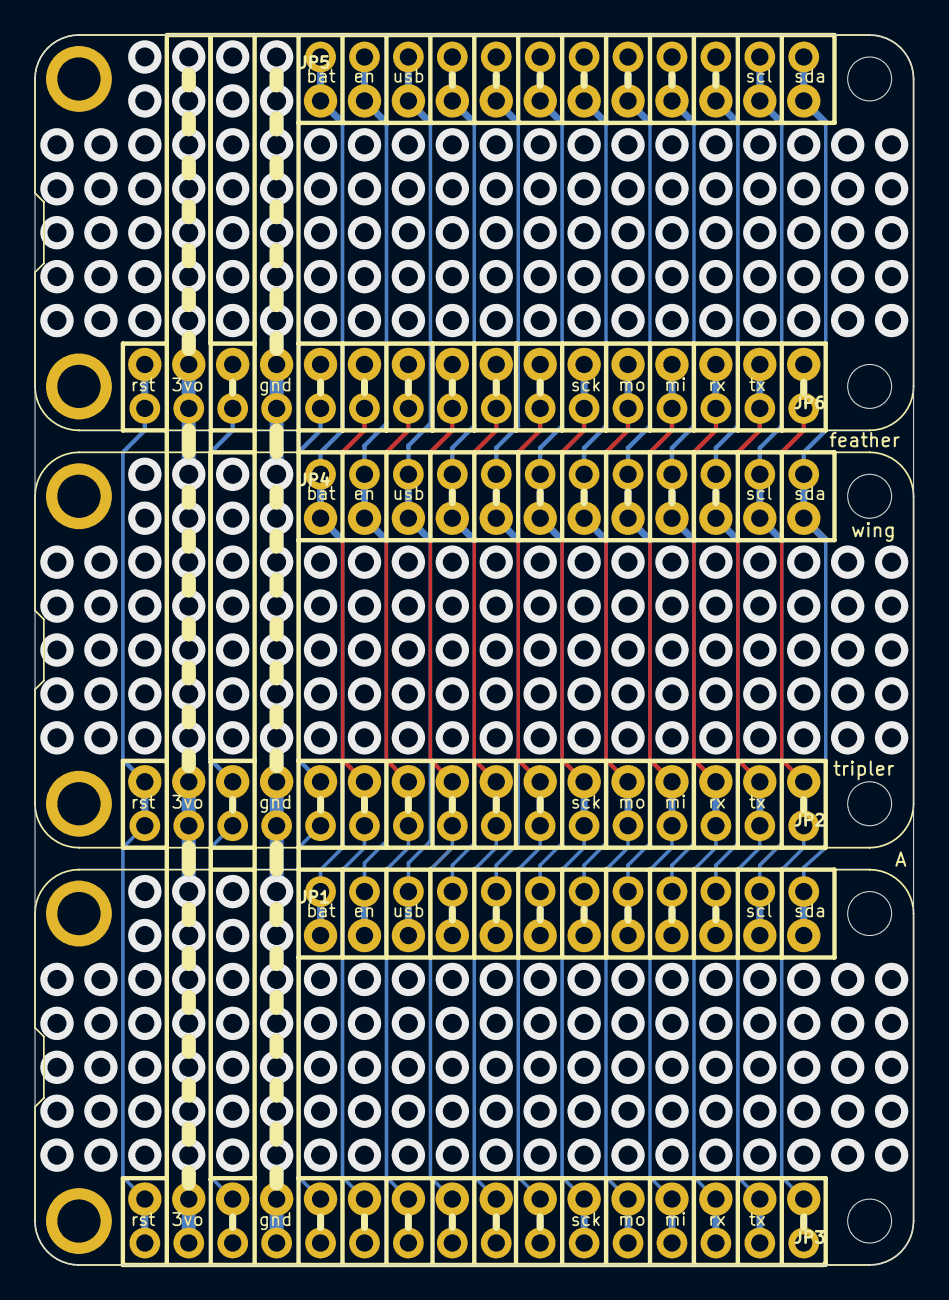
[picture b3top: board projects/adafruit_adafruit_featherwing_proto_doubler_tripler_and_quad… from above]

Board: 2 copper layers, 50.8 x 71.1 mm, 9 parts (0 on the bottom side), 28 nets.

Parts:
JP1, JP4, JP5: 1X12_ROUND_76MIL
JP2, JP3, JP6: 1X16_ROUND_76MIL
MS1, MS2, MS3: FEATHERWING_NODIM; FEATHERWING_DIM

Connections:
3V: JP2.15, JP3.15, JP6.15, MS1.2, MS2.2, MS3.2
A: JP2.12, JP3.12, JP6.12, MS1.5, MS2.5, MS3.5
AREF: JP2.14, JP3.14, JP6.14, MS1.3, MS2.3, MS3.3
B: JP2.11, JP3.11, JP6.11, MS1.6, MS2.6, MS3.6
C: JP2.10, JP3.10, JP6.10, MS1.7, MS2.7, MS3.7
D: JP2.9, JP3.9, JP6.9, MS1.8, MS2.8, MS3.8
E: JP2.8, JP3.8, JP6.8, MS1.9, MS2.9, MS3.9
EN: JP1.2, JP4.2, JP5.2, MS1.27, MS2.27, MS3.27
F: JP2.7, JP3.7, JP6.7, MS1.10, MS2.10, MS3.10
G: JP2.1, JP3.1, JP6.1, MS1.16, MS2.16, MS3.16
GND: JP2.13, JP3.13, JP6.13, MS1.4, MS2.4, MS3.4
I: JP1.9, JP4.9, JP5.9, MS1.20, MS2.20, MS3.20
J: JP1.10, JP4.10, JP5.10, MS1.19, MS2.19, MS3.19
K: JP1.8, JP4.8, JP5.8, MS1.21, MS2.21, MS3.21
L: JP1.7, JP4.7, JP5.7, MS1.22, MS2.22, MS3.22
M: JP1.6, JP4.6, JP5.6, MS1.23, MS2.23, MS3.23
MISO: JP2.4, JP3.4, JP6.4, MS1.13, MS2.13, MS3.13
MOSI: JP2.5, JP3.5, JP6.5, MS1.12, MS2.12, MS3.12
N: JP1.5, JP4.5, JP5.5, MS1.24, MS2.24, MS3.24
O: JP1.4, JP4.4, JP5.4, MS1.25, MS2.25, MS3.25
RESET: JP2.16, JP3.16, JP6.16, MS1.1, MS2.1, MS3.1
RX: JP2.3, JP3.3, JP6.3, MS1.14, MS2.14, MS3.14
SCK: JP2.6, JP3.6, JP6.6, MS1.11, MS2.11, MS3.11
SCL: JP1.11, JP4.11, JP5.11, MS1.18, MS2.18, MS3.18
SDA: JP1.12, JP4.12, JP5.12, MS1.17, MS2.17, MS3.17
TX: JP2.2, JP3.2, JP6.2, MS1.15, MS2.15, MS3.15
USB: JP1.3, JP4.3, JP5.3, MS1.26, MS2.26, MS3.26
VBAT: JP1.1, JP4.1, JP5.1, MS1.28, MS2.28, MS3.28

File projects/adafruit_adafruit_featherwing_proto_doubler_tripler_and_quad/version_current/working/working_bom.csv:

Row,Description,Part,References,Value,Footprint,Quantity Per PCB,Status,Datasheet
1,,HEADER-1X1276MIL,JP1 JP4 JP5,HEADER-1X1276MIL,1X12_ROUND_76MIL,3, ,
2,,HEADER-1X16_76MIL,JP2 JP3 JP6,HEADER-1X16_76MIL,1X16_ROUND_76MIL,3, ,
3,,FEATHERWING_NODIM,MS1 MS2 MS3,FEATHERWING_NODIM,FEATHERWING_DIM,3, ,





Project info:
Schematic:,working
Variant:,default
Revision:,
Date:,2023-08-02_17-08-33
KiCad Version:,7.0.6-7.0.6~ubuntu22.04.1
Statistics:
Component Groups:,3
Component Count:,9 (0 SMD/ 0 THT)
Fitted Components:,9 (0 SMD/ 0 THT)
Number of PCBs:,1
Total Components:,9
